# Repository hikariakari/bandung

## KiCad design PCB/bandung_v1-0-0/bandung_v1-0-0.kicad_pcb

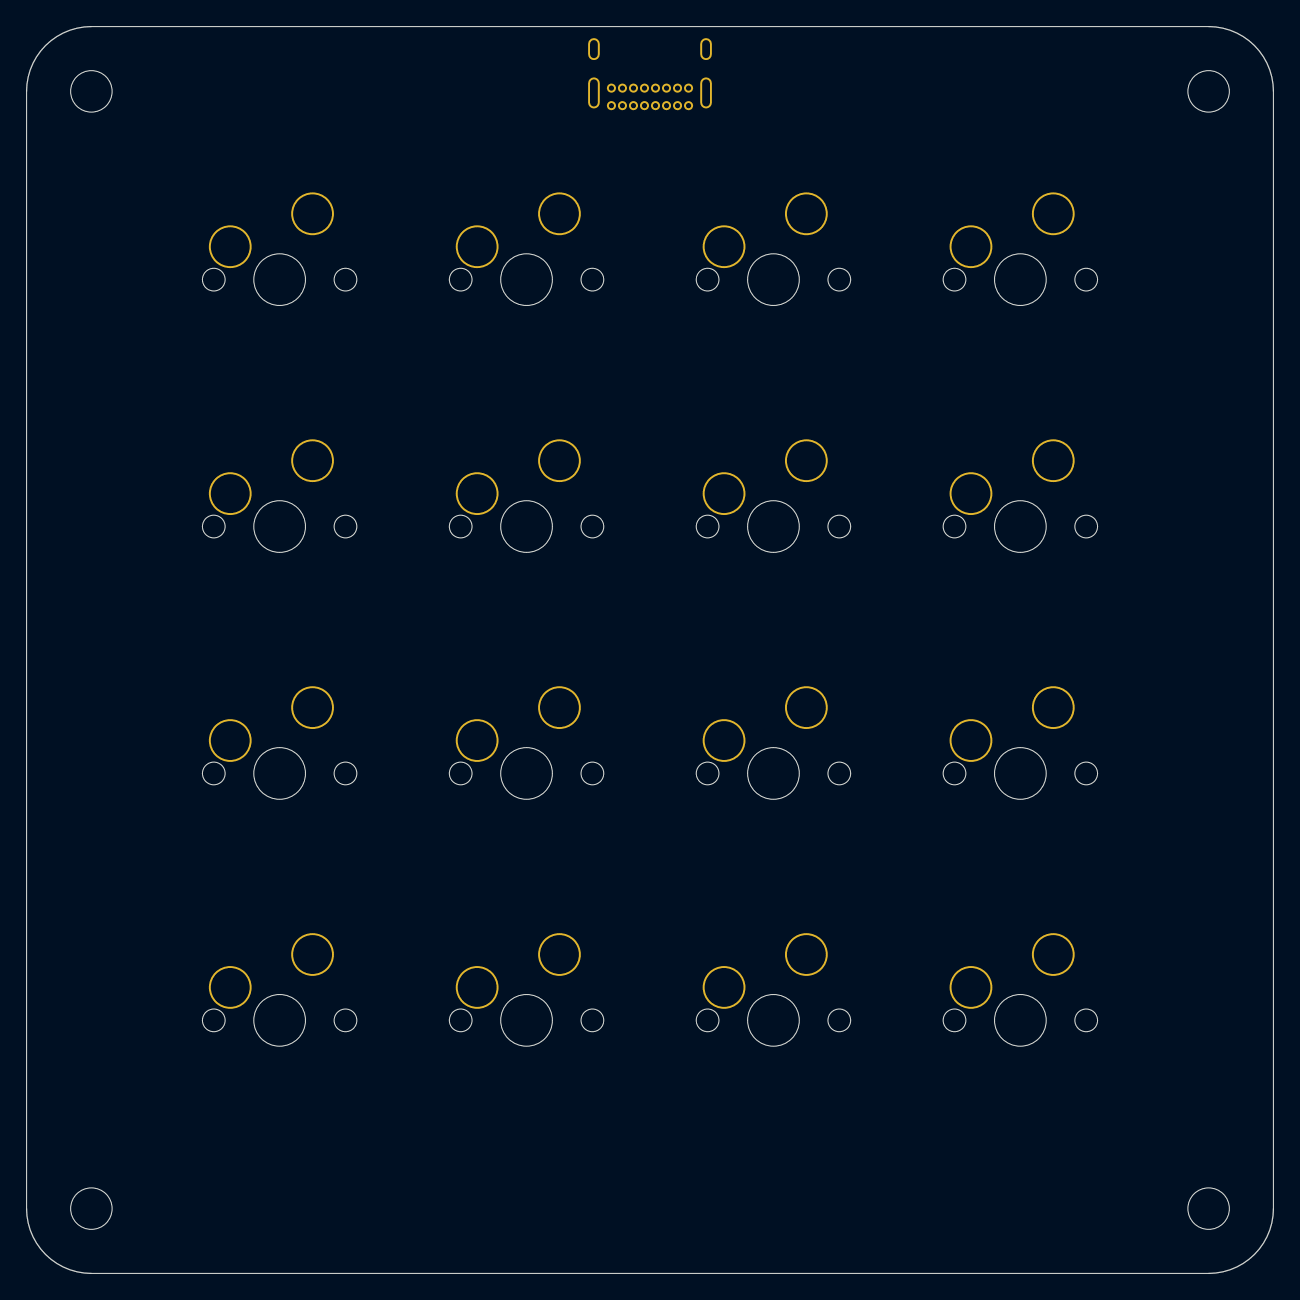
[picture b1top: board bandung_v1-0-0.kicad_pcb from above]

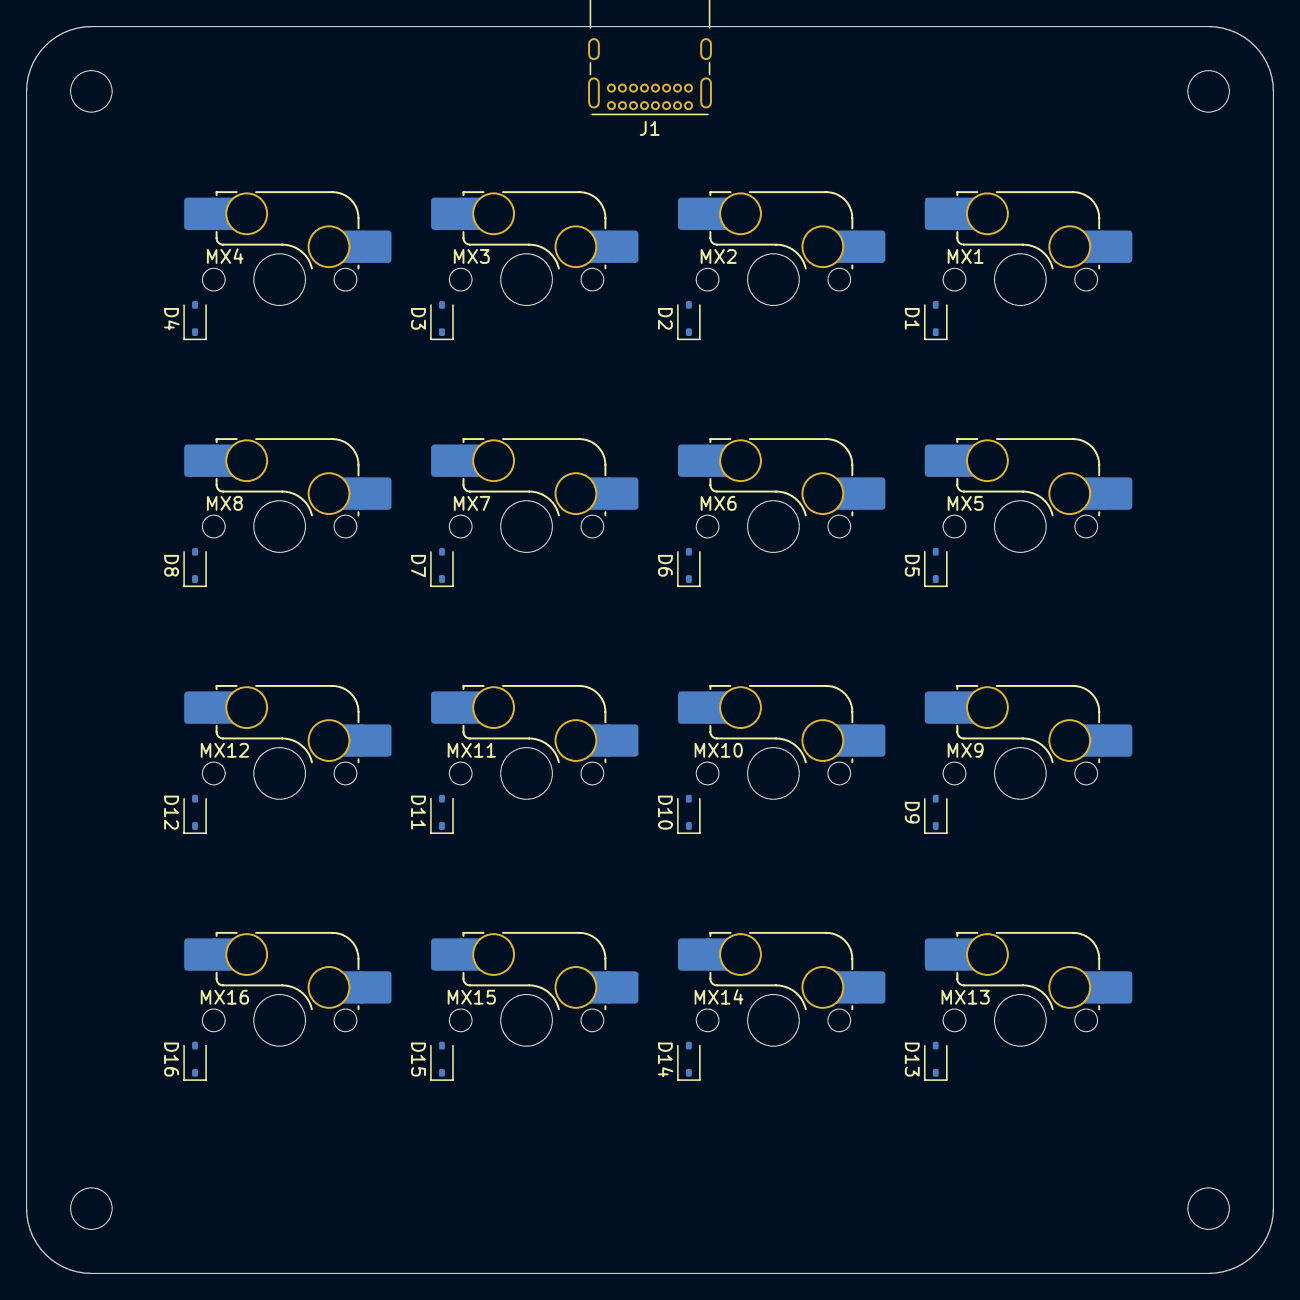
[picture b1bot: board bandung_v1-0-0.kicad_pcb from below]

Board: 2 copper layers, 96.2 x 96.2 mm, 37 parts (33 on the bottom side), 26 nets, no tracks yet.

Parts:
D1, D2, D3, D4, D5, D6, D7, D8, D9, D10, D11, D12, D13, D14, D15, D16: 1N5819WS; D_SOD-323
H1, H2, H3, H4: MountingHole; MountingHole_3.2mm_M3
J1: USB_C_Receptacle_USB2.0_16P; USB_C_Receptacle_GCT_USB4085
MX1, MX2, MX3, MX4, MX5, MX6, MX7, MX8, MX9, MX10, MX11, MX12, MX13, MX14, MX15, MX16: MX_SW_HS; SW_MX_HS_CPG151101S11_1u

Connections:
unnamed: D1.2 (A), MX1.2
unnamed: D1.1 (K), D2.1 (K), D3.1 (K), D4.1 (K)
unnamed: D2.2 (A), MX2.2
unnamed: D3.2 (A), MX3.2
unnamed: D4.2 (A), MX4.2
unnamed: D5.2 (A), MX5.2
unnamed: D5.1 (K), D6.1 (K), D7.1 (K), D8.1 (K)
unnamed: D6.2 (A), MX6.2
unnamed: D7.2 (A), MX7.2
unnamed: D8.2 (A), MX8.2
unnamed: D9.2 (A), MX9.2
unnamed: D10.2 (A), MX10.2
unnamed: D9.1 (K), D10.1 (K), D11.1 (K), D12.1 (K)
unnamed: D11.2 (A), MX11.2
unnamed: D12.2 (A), MX12.2
unnamed: D13.2 (A), MX13.2
unnamed: D13.1 (K), D14.1 (K), D15.1 (K), D16.1 (K)
unnamed: D14.2 (A), MX14.2
unnamed: D15.2 (A), MX15.2
unnamed: D16.2 (A), MX16.2
unnamed: J1.A1 (GND), J1.A12 (GND), J1.B1 (GND), J1.B12 (GND)
unnamed: J1.A4 (VBUS), J1.A9 (VBUS), J1.B4 (VBUS), J1.B9 (VBUS)
unnamed: MX1.1, MX5.1, MX9.1, MX13.1
unnamed: MX2.1, MX6.1, MX10.1, MX14.1
unnamed: MX3.1, MX7.1, MX11.1, MX15.1
unnamed: MX4.1, MX8.1, MX12.1, MX16.1

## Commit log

2024-06-18 PCB design is still in progress
